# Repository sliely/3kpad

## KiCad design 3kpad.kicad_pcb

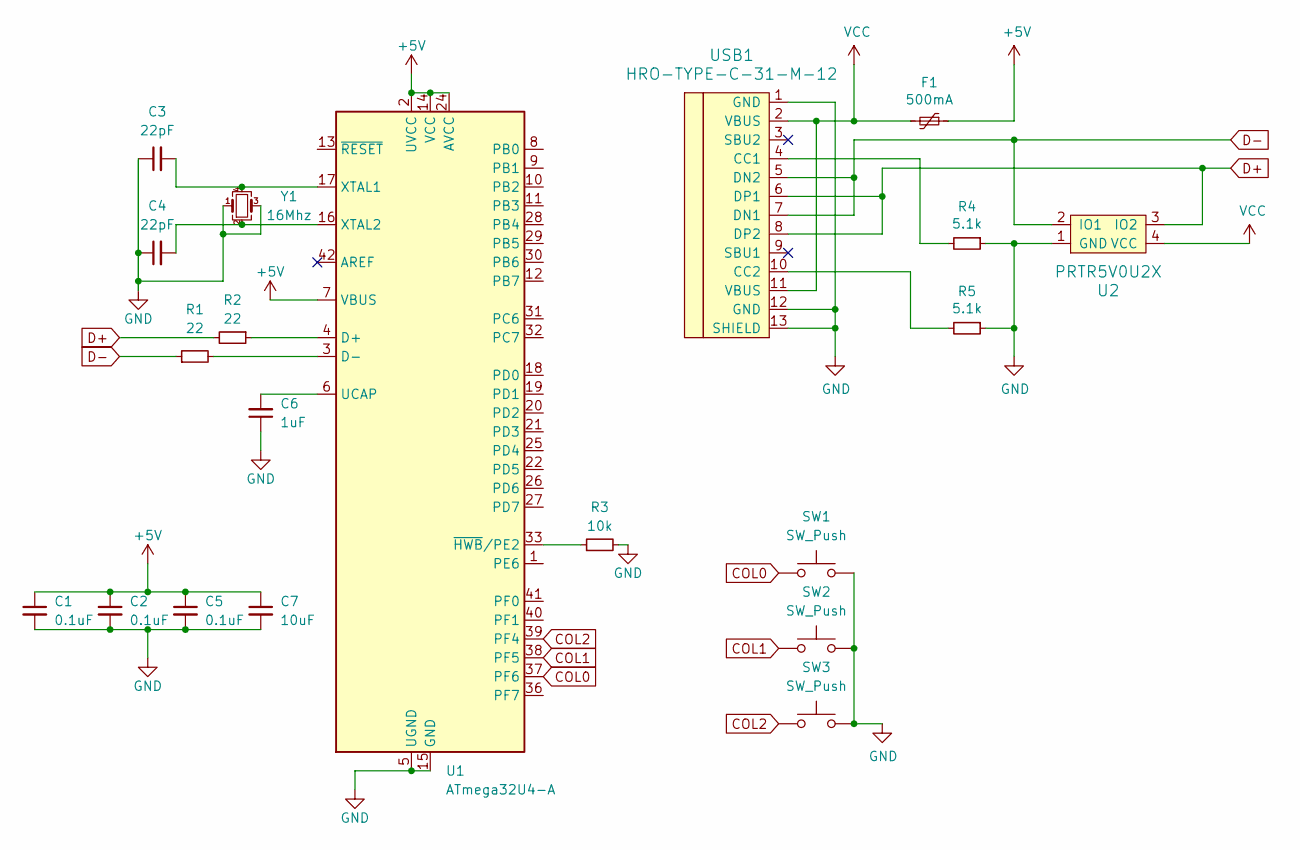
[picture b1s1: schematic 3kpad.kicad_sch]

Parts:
C1, C2, C5: 0.1uF; C_0805_2012Metric; LCSC C49678
C3, C4: 22pF; C_0805_2012Metric; LCSC C1804
C6: 1uF; C_0805_2012Metric; LCSC C28323
C7: 10uF; C_0805_2012Metric; LCSC C15850
F1: 500mA; Fuse_1206_3216Metric; LCSC C70069
R1, R2: 22; R_0805_2012Metric; LCSC C17561
R3: 10k; R_0805_2012Metric; LCSC C17414
R4, R5: 5.1k; R_0805_2012Metric; LCSC C27834
SW1, SW2, SW3: SW_Push; MX-Hotswap-1U
U1: ATmega32U4-A; TQFP-44_10x10mm_P0.8mm; LCSC C44854
U2: PRTR5V0U2X; SOT143B; LCSC C12333
USB1: HRO-TYPE-C-31-M-12; HRO-TYPE-C-31-M-12-HandSoldering; LCSC C165948
Y1: 16Mhz; Crystal_SMD_3225-4Pin_3.2x2.5mm; LCSC C156247

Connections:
+5V: C1.1, C2.1, C5.1, C7.1, F1.1, U1.2 (UVCC), U1.7 (VBUS), U1.14 (VCC), U1.24 (AVCC), U1.34 (VCC), U1.44 (AVCC)
COL0: SW1.1, U1.37 (PF6)
COL1: SW2.1, U1.38 (PF5)
COL2: SW3.1, U1.39 (PF4)
D+: R2.2, U2.3 (IO2), USB1.6 (DP1), USB1.8 (DP2)
D-: R1.1, U2.2 (IO1), USB1.5 (DN2), USB1.7 (DN1)
GND: C1.2, C2.2, C3.1, C4.1, C5.2, C6.1, C7.2, R3.2, R4.1, R5.1, SW1.2, SW2.2, SW3.2, U1.5 (UGND), U1.15 (GND), U1.23 (GND), U1.35 (GND), U1.43 (GND), U2.1 (GND), USB1.1 (GND), USB1.12 (GND), USB1.13 (SHIELD), Y1.1, Y1.3
unnamed: C3.2, U1.17 (XTAL1), Y1.4
unnamed: C4.2, U1.16 (XTAL2), Y1.2
unnamed: C6.2, U1.6 (UCAP)
unnamed: R1.2, U1.3 (D-)
unnamed: R2.1, U1.4 (D+)
unnamed: R3.1, U1.33 (~HWB/PE2)
unnamed: R4.2, USB1.4 (CC1)
unnamed: R5.2, USB1.10 (CC2)
VCC: F1.2, U2.4 (VCC), USB1.2 (VBUS), USB1.11 (VBUS)

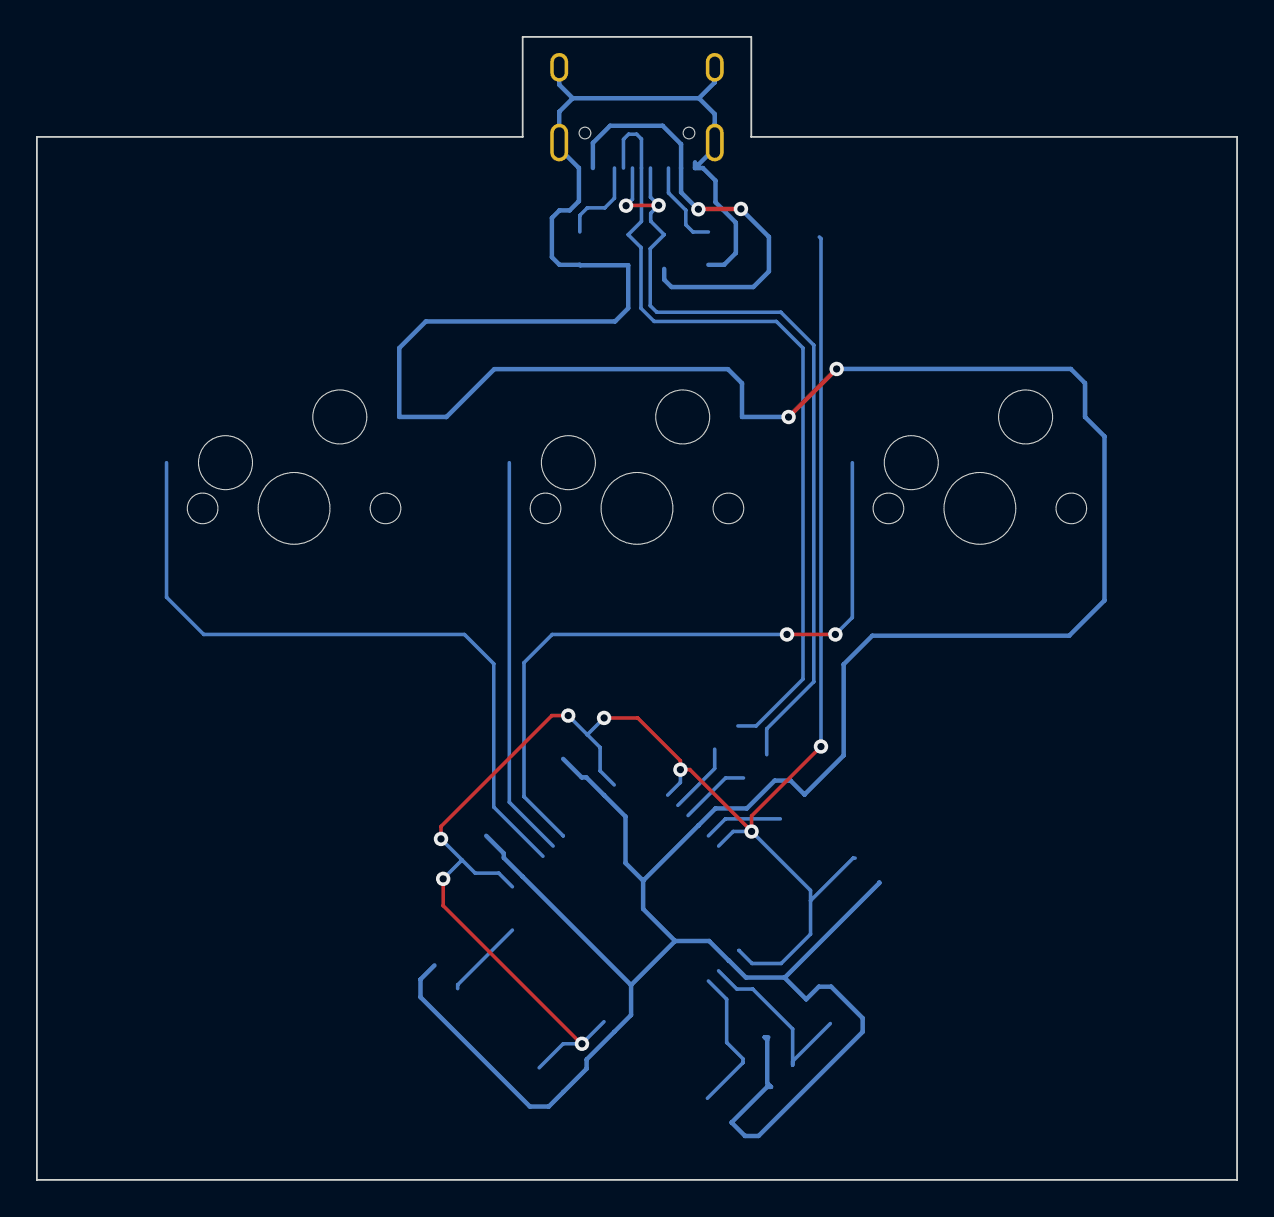
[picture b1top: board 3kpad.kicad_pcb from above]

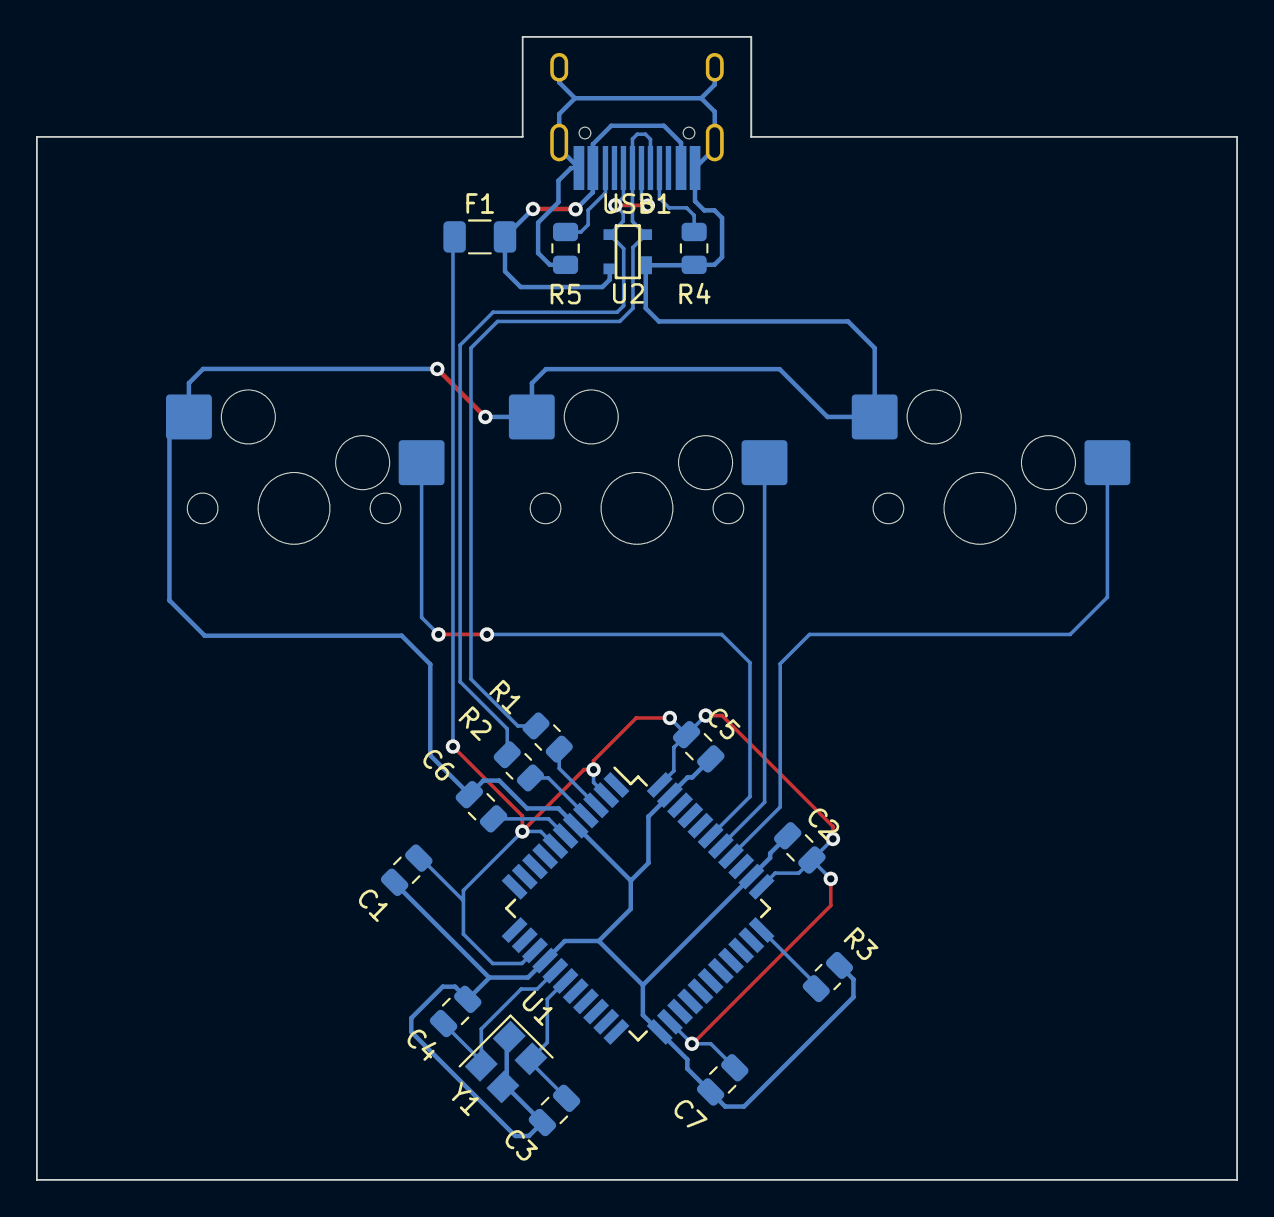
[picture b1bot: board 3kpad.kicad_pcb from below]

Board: 2 copper layers, 66.7 x 63.5 mm, 20 parts (17 on the bottom side), 16 nets.

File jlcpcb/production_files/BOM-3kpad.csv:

Comment,Designator,Footprint,LCSC
PRTR5V0U2X,U2,SOT143B,C12333
16Mhz,Y1,Crystal_SMD_3225-4Pin_3.2x2.5mm,C156247
10uF,C7,C_0805_2012Metric,C15850
HRO-TYPE-C-31-M-12,USB1,HRO-TYPE-C-31-M-12-HandSoldering,C165948
10k,R3,R_0805_2012Metric,C17414
22,"R1,R2",R_0805_2012Metric,C17561
22pF,"C3,C4",C_0805_2012Metric,C1804
5.1k,"R4,R5",R_0805_2012Metric,C27834
1uF,C6,C_0805_2012Metric,C28323
ATmega32U4-A,U1,TQFP-44_10x10mm_P0.8mm,C44854
0.1uF,"C1,C2,C5",C_0805_2012Metric,C49678
500mA,F1,Fuse_1206_3216Metric,C70069
SW_Push,SW2,MX-Hotswap-1U,
SW_Push,SW1,MX-Hotswap-1U,
SW_Push,SW3,MX-Hotswap-1U,

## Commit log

2023-02-10 fix something(idk)
